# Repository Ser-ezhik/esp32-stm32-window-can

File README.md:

# ESP32 + STM32 window and door controller

New hardware generation of the original `esp32-rp2040-window-rs485` project.
The legacy source and all historic firmware releases remain in Git history and
under the `legacy-rp2040-import` tag. New releases never replace previous binaries.

## Target architecture

- ESP32-S3: CC1101 433 MHz radio, Wi-Fi, web UI, configuration backup and CAN coordinator.
- One cabinet per physical window or door.
- One universal STM32F103C8T6 master in each cabinet: two VNH5019A-E channels, CAN,
  CAP1188 over 4-wire SPI, three D-M9 position sensors and up to three local UART slaves.
- Up to three identical STM32 boards as local slaves, two VNH5019A-E channels per board.
- One firmware image for every STM32 board. `SLOT_ID` pins on the cabinet carrier select
  master/slave role, so a pre-flashed spare module can replace any controller.
- Cabinet identity is stored in a 25LCxx SPI EEPROM on the non-removable carrier board.

## Current development status

The current releases are STM32 two-channel `0.1.0-alpha.14`, STM32 four-channel
`0.1.0-alpha.13`, and ESP32-S3 `0.1.0-alpha.12`:

- hardware bxCAN at 500 kbit/s;
- three hardware UART links at 250 kbit/s with CRC16 frames;
- VNH5019A-E PWM, direction, current sense and diagnostic monitoring;
- CAP1188 4-wire SPI driver, no I2C;
- three active-low D-M9N inputs;
- current disappearance end-stop detection;
- overcurrent, no-current, timeout, edge and communication fail-safe states;
- per-direction full-stroke calibration data and PWM equalization;
- carrier provisioning/discovery protocol;
- watchdog and safe outputs at boot.
- bounded CAN/UART receive work per control-loop pass;
- validation of command, fault and object-type values received from the bus;
- verified internal configuration writes with retries and a latched storage fault;
- ESP32-S3 CAN coordinator with CC1101 receiver and configuration stored in NVS;
- object-based web UI for up to 64 windows/doors, actuator telemetry, events and emergency stop;
- editable 433 MHz button assignments;
- separate open/close calibration, position-aware full-cycle calibration and calibration reset;
- per-input D-M9N/D-M9P polarity stored in the cabinet carrier EEPROM.

The `alpha.1` STM32 binaries and tag remain unchanged. `alpha.2` is a new release
because the CAN protocol gained a calibration-reset command.

ESP32 `alpha.3` fixes mobile-width overflow found during Chrome testing. The
wide actuator table now scrolls inside its own container without widening the page.

ESP32 `alpha.4` targets the tested ESP32-S3 N16R8 module: 16 MB quad Flash,
PSRAM disabled (the firmware does not need it), and a 3 MB application partition. It also prints startup diagnostics
at 115200 baud. This hardware is verified with Arduino-ESP32 core `3.0.7`;
do not use core `3.3.8` for it because Wi-Fi startup is unstable on the tested board.
Generic 4 MB images remain archived under their original tags.

## Build STM32 firmware

Install Arduino CLI and the official STM32 core, then run:

```powershell
arduino-cli compile `
  --fqbn "STMicroelectronics:stm32:GenF1:pnum=GENERIC_F103C8TX,xserial=none,usb=none,opt=oslto,dbg=none,rtlib=nano" `
  --libraries libraries `
  --export-binaries `
  ArduinoIDE\STM32_Universal_Actuator_Node
```

The project deliberately targets the real 64 KiB capacity of STM32F103C8T6 and
does not rely on unofficial 128 KiB clone behaviour.

## Build ESP32-S3 firmware

```powershell
powershell -ExecutionPolicy Bypass -File tools\embed-web.ps1
arduino-cli core install esp32:esp32@3.0.7
arduino-cli compile `
  --fqbn "esp32:esp32:esp32s3:FlashMode=dio,FlashSize=16M,PartitionScheme=app3M_fat9M_16MB,PSRAM=disabled" `
  --libraries libraries `
  --export-binaries ArduinoIDE\ESP32_CC1101_CAN_Master
```

The current web interface intentionally exposes only full open, full close and
stop. A partial ventilation command will be added only after its position rule
or dedicated sensor is defined and bench-tested.

## Documentation

- `docs/HARDWARE_ARCHITECTURE.md`
- `docs/CAN_PROTOCOL.md`
- `docs/SAFETY_AND_RECOVERY.md`
- `docs/BOM_v0.1.md`
- `hardware/DOOR-8CH/README.md`
- `hardware/WINDOW-4CH/README.md`

This is safety-related motion-control software. Test with disconnected mechanics
and current-limited power before connecting a door or window.

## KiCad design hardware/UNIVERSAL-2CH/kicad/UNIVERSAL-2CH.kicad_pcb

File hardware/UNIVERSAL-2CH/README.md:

# UNIVERSAL-2CH

Compact universal carrier for two 12 V linear actuators. The same assembled
board can be provisioned as an optional sliding-door drive or as a two-actuator
vent/window node.

## Hardware

- Board: 106 x 112 mm, four copper layers.
- Controller: one socketed STM32F103C8T6 Mini.
- Drivers: two VNH5019A-E channels with mounting holes for top heatsinks.
- Network: socketed SN65HVD230 CAN transceiver module and protected edge entry.
- Touch safety: optional socketed CAP1188 SPI module with three field inputs.
- Position: three protected reed-switch inputs.
- Identity and journal: 25LC256 carrier EEPROM.
- Supply: socketed MP1584 12 V to 5 V converter, 3.3 V regulator, power-good
  monitor, and logic hold-up capacitor.

## Connectors

- `J1`, `J2`: actuator connectors, `+12V / GND / MA / MB`.
- `J201` to `J203`: open, closed, and in-place reed sensors.
- `J211` to `J213`: capacitive field sensors.
- `J230`: protected 12 V logic input.
- `J240`: `CANH / CANL / GND / shield`.
- `J220`: SWD service header.

All external field connectors are placed on board edges. Power routing and
VNH5019 devices occupy the upper half; CAN and touch electronics are kept away
from the motor outputs.

The field interfaces use board-mounted male headers with removable female cable
plugs. Connector fronts face outwards; the layout includes body clearance
between adjacent plugs and keeps the cable-entry space outside the board edge.

## KiCad Files

- `kicad/UNIVERSAL-2CH.kicad_pcb`: routed PCB.
- `kicad/UNIVERSAL-2CH.kicad_sch`: complete flat schematic.
- `kicad/UNIVERSAL-2CH-multisheet.kicad_sch`: multisheet root schematic.
- `kicad/UNIVERSAL-2CH-routed-top.png`: final top-side 3D render.
- `kicad/UNIVERSAL-2CH-routed-iso.png`: final isometric 3D render.
- `UNIVERSAL-2CH-BOM.csv`: grouped BOM.

## Verification

- PCB DRC: 0 violations, 0 unconnected items.
- Flat schematic ERC: 0 errors, 0 warnings.
- Multisheet schematic ERC: 0 errors, 0 warnings.
- PCB-to-schematic sync: 90 references, 283 connected pads, 38 explicit NCs.
- Routing geometry: straight segments with 45-degree transitions; no staircase
  routing on long connections.
- STM32 pin audit: 27 functional socket connections match `config.h`.
- STM32 build: 24,136 bytes Flash (36%), 3,500 bytes RAM (17%).

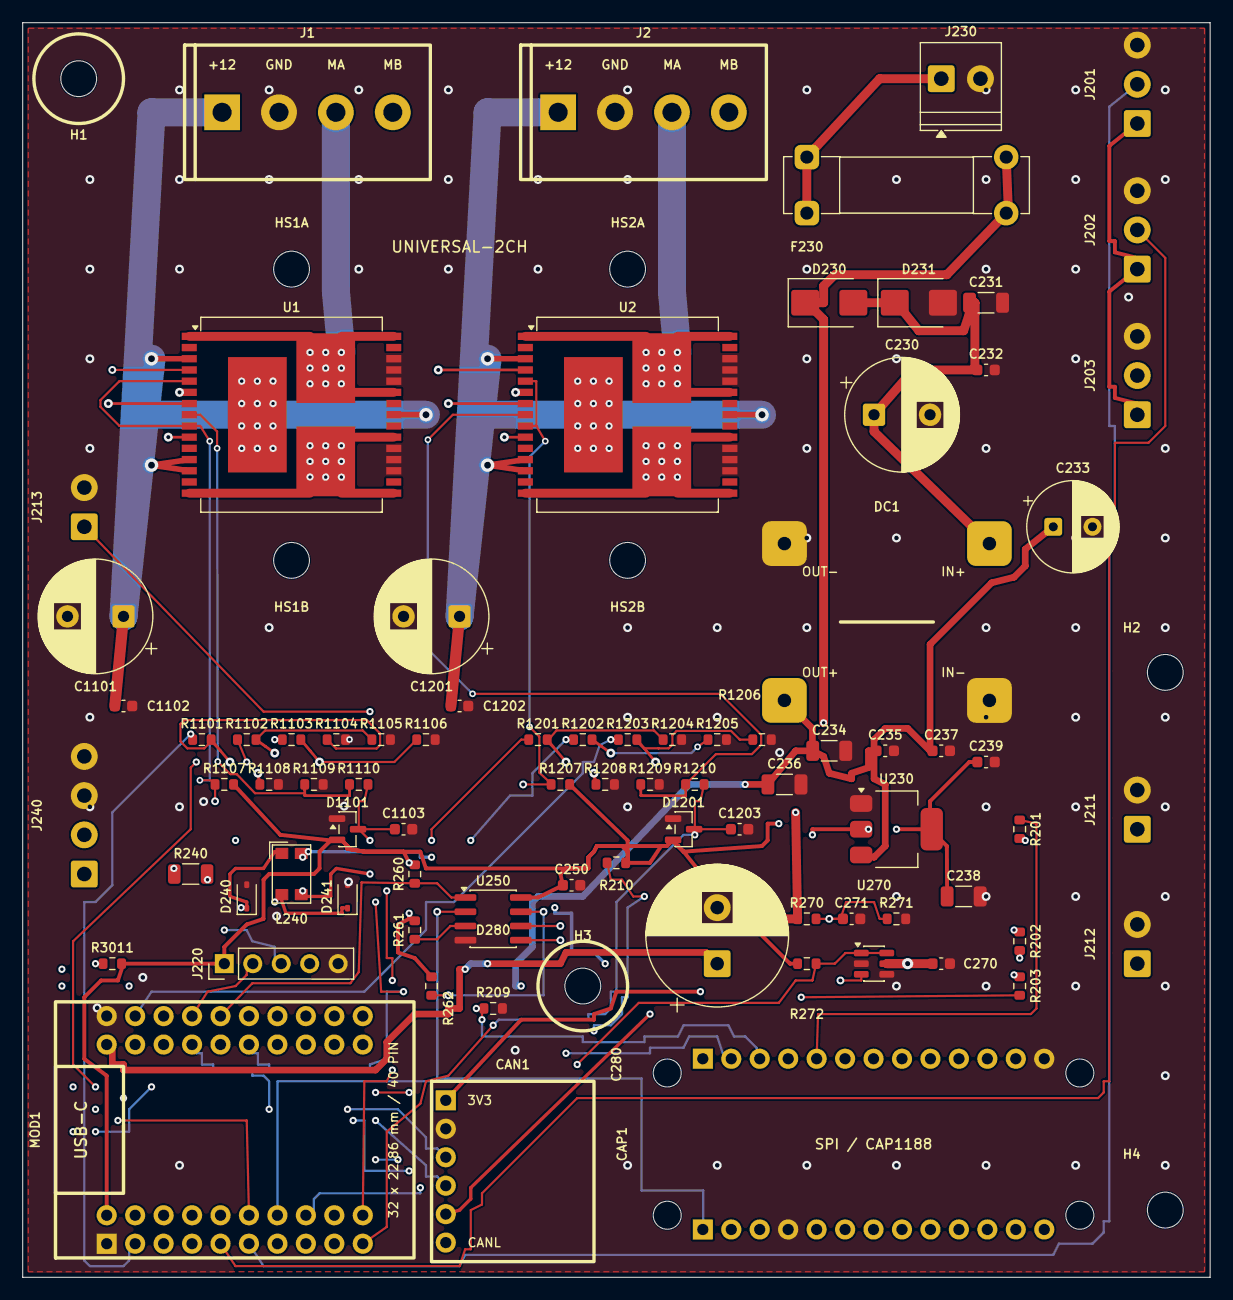
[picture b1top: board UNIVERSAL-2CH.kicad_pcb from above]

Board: 4 copper layers, 106.0 x 112.0 mm, 90 parts (1 on the bottom side), 64 nets.

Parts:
C230: 470UF_50V; CP_Radial_D10.0mm_P5.00mm
C231: 1UF_50V; C_1206_3216Metric
C232: 100NF_50V; C_0603_1608Metric
C233: 220UF_10V; CP_Radial_D8.0mm_P3.50mm
C234: 10UF_10V; C_1206_3216Metric
C235: 100NF_16V; C_0603_1608Metric
C236: 10UF_10V_3V3_IN; C_1206_3216Metric
C237: 100NF_16V_3V3_IN; C_0603_1608Metric
C238: 10UF_10V_3V3_OUT; C_1206_3216Metric
C239: 100NF_16V_3V3_OUT; C_0603_1608Metric
C250: 100NF_EEPROM; C_0603_1608Metric
C270: 100NF_25V_PGOOD_VDD; C_0603_1608Metric
C271: 100NF_PGOOD_FILTER; C_0603_1608Metric
C280: 4700UF_10V_LOW_ESR_S1_HOLDUP; CP_Radial_D12.5mm_P5.00mm
C1101, C1201: 470uF 35V LOW_ESR; CP_Radial_D10.0mm_P5.00mm
C1102, C1202: 100nF 50V X7R VCC; C_0603_1608Metric
C1103, C1203: 100nF ADC_FILTER; C_0603_1608Metric
CAN1: SN65HVD230_MASTER_CAN; SN65HVD230_Module_14.5x16.1mm_1x06
CAP1: CAP1188_SPI; CAP1188_Adafruit1602_Module_2x13
D230: SS54_REVERSE_POLARITY; D_SMB
D231: SMBJ16A_TVS; D_SMB
D240: PESD1CAN_CANH; D_SOD-323
D241: PESD1CAN_CANL; D_SOD-323
D280: SS34_S1_HOLDUP_ISOLATION; D_SMA
D1101, D1201: BAT54S ADC_CLAMP; SOT-23
DC1: MP1584_FIXED_5V; MP1584_Fixed5V_Module_22.3x17mm
F230: 1A_SLOW_5X20; Fuseholder_Clip-5x20mm_Bel_FC-203-22_Lateral_P17.80x5.00mm_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
H1, H2, H3, H4: M3.2_NPTH; MountingHole_M3_2_NPTH
HS1A, HS1B, HS2A, HS2B: M3.2 NPTH, TOP HEATSINK; MountingHole_3.2mm_M3
J1: ACTUATOR_CH1_4P; DINKLE_2EHDRC-04P_P5.08mm
J2: ACTUATOR_CH2_4P; DINKLE_2EHDRC-04P_P5.08mm
J201: REED_A_OPEN_3V3_SIG_GND; TerminalBlock_Phoenix_PT-1,5-3-3.5-H_1x03_P3.50mm_Horizontal
J202: REED_A_CLOSED_3V3_SIG_GND; TerminalBlock_Phoenix_PT-1,5-3-3.5-H_1x03_P3.50mm_Horizontal
J203: REED_A_IN_PLACE_3V3_SIG_GND; TerminalBlock_Phoenix_PT-1,5-3-3.5-H_1x03_P3.50mm_Horizontal
J211: CAP_CS1_GND; TerminalBlock_Phoenix_PT-1,5-2-3.5-H_1x02_P3.50mm_Horizontal
J212: CAP_CS2_GND; TerminalBlock_Phoenix_PT-1,5-2-3.5-H_1x02_P3.50mm_Horizontal
J213: CAP_CS3_GND; TerminalBlock_Phoenix_PT-1,5-2-3.5-H_1x02_P3.50mm_Horizontal
J220: SWD_S1_3V3_DIO_CLK_NRST_GND; PinHeader_1x05_P2.54mm_Vertical
J230: LOGIC_12V_GND; TerminalBlock_Phoenix_PT-1,5-2-3.5-H_1x02_P3.50mm_Horizontal
J240: CANH_CANL_GND_SHIELD; TerminalBlock_Phoenix_PT-1,5-4-3.5-H_1x04_P3.50mm_Horizontal
L240: CMC_CAN; L_CommonModeChoke_Coilcraft_1812CAN
MOD1: STM32F103C8T6_MINI_SLOT_S1; STM32F103C8T6_Mini_CH340_4x10
R201, R202, R203: 1K_CAP_INPUT; R_0603_1608Metric
R209: 10K_CAP_RESET_PULLDOWN; R_0603_1608Metric
R210: 10K_CAP_IRQ_PULLUP; R_0603_1608Metric
R240: 120R_CAN_TERM_DNP; R_1206_3216Metric
R260: 10K_EEPROM_CS_PULLUP; R_0603_1608Metric
R261: 10K_EEPROM_WP_PULLUP; R_0603_1608Metric
R262: 10K_EEPROM_HOLD_PULLUP; R_0603_1608Metric
R270: 226K_1%_PGOOD_TOP; R_0603_1608Metric
R271: 10K_1%_PGOOD_BOTTOM; R_0603_1608Metric
R272: 10K_PGOOD_PULLUP; R_0603_1608Metric
R1101, R1201: 100R INA_SER; R_0603_1608Metric
R1102, R1202: 100R INB_SER; R_0603_1608Metric
R1103, R1203: 100R PWM_SER; R_0603_1608Metric
R1104, R1204: 10K INA_PULLDOWN; R_0603_1608Metric
R1105, R1205: 10K INB_PULLDOWN; R_0603_1608Metric
R1106, R1206: 10K PWM_PULLDOWN; R_0603_1608Metric
R1107, R1207: 4K7 DIAG_PULLUP; R_0603_1608Metric
R1108, R1208: 10K CS_DIS_PULLDOWN; R_0603_1608Metric
R1109, R1209: 1K 1% CS_LOAD; R_0603_1608Metric
R1110, R1210: 10K ADC_SERIES; R_0603_1608Metric
R3011: 47K SLOT_S1_ID0; R_0603_1608Metric
U1, U2: VNH5019A-E; ST_MultiPowerSO-30
U230: AMS1117-3V3; SOT-223-3_TabPin2
U250: 25LC256_SOIC8_CARRIER_ID; SOIC-8_3.9x4.9mm_P1.27mm
U270: TLV6700DDCR_POWER_MONITOR; SOT-23-6

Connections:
CANH_BUS: CAN1.5, L240.4, R240.1
CANH_ENTRY: D240.1, J240.1, L240.1
CANL_BUS: CAN1.6, L240.3, R240.2
CANL_ENTRY: D241.1, J240.2, L240.2
CAP_C1_FIELD: J211.1, R201.2
CAP_C1_RAW: CAP1.18, R201.1
CAP_C2_FIELD: J212.1, R202.2
CAP_C2_RAW: CAP1.19, R202.1
CAP_C3_FIELD: J213.1, R203.2
CAP_C3_RAW: CAP1.20, R203.1
CAP_CS: CAP1.15, MOD1.18
CAP_IRQ: MOD1.13, R210.1
CAP_MISO: CAP1.1, MOD1.17, U250.2
CAP_MOSI: CAP1.14, MOD1.7, U250.5
CAP_RESET: CAP1.16, MOD1.29, R209.1
CAP_SCK: CAP1.2, MOD1.8, U250.6
CH1_CS_DIS: R1108.1, U1.6
CH1_CS_RAW: R1109.1, R1110.1, U1.8
CH1_CURRENT_ADC: C1103.1, D1101.3, MOD1.20, R1110.2
CH1_DIAG: MOD1.27, R1107.1, U1.5, U1.9
CH1_INA: R1101.2, R1104.1, U1.4
CH1_INA_MCU: MOD1.2, R1101.1
CH1_INB: R1102.2, R1105.1, U1.10
CH1_INB_MCU: MOD1.12, R1102.1
CH1_OUTA: J1.3, U1.1, U1.25, U1.30, U1.33
CH1_OUTB: J1.4, U1.15, U1.16, U1.21, U1.32
CH1_PWM: R1103.2, R1106.1, U1.7
CH1_PWM_MCU: MOD1.22, R1103.1
CH2_CS_DIS: R1208.1, U2.6
CH2_CS_RAW: R1209.1, R1210.1, U2.8
CH2_CURRENT_ADC: C1203.1, D1201.3, MOD1.10, R1210.2
CH2_DIAG: MOD1.3, R1207.1, U2.5, U2.9
CH2_INA: R1201.2, R1204.1, U2.4
CH2_INA_MCU: MOD1.26, R1201.1
CH2_INB: R1202.2, R1205.1, U2.10
CH2_INB_MCU: MOD1.36, R1202.1
CH2_OUTA: J2.3, U2.1, U2.25, U2.30, U2.33
CH2_OUTB: J2.4, U2.15, U2.16, U2.21, U2.32
CH2_PWM: R1203.2, R1206.1, U2.7
CH2_PWM_MCU: MOD1.32, R1203.1
EEPROM_CS: MOD1.35, R260.1, U250.1
EEPROM_HOLD: R262.1, U250.7
EEPROM_WP: R261.1, U250.3
FUSED_12V_CH1: C1101.1, C1102.1, J1.1, U1.3, U1.12, U1.13, U1.23, U1.31
FUSED_12V_CH2: C1201.1, C1202.1, J2.1, U2.3, U2.12, U2.13, U2.23, U2.31
GND: C230.2, C231.2, C232.2, C233.2, C234.2, C235.2, C236.2, C237.2, C238.2, C239.2, C250.2, C270.2, C271.2, C280.2, C1101.2, C1102.2, C1103.2, C1201.2, C1202.2, C1203.2, CAN1.2, CAP1.4, CAP1.26, D231.2, D240.2, D241.2, D1101.1, D1201.1, DC1.2, DC1.4, J1.2, J2.2, J201.3, J202.3, J203.3, J211.2, J212.2, J213.2, J220.5, J230.2, J240.3, J240.4, MOD1.1, MOD1.31, R209.2, R271.2, R1104.2, R1105.2, R1106.2, R1108.2, R1109.2, R1204.2, R1205.2, R1206.2, R1208.2, R1209.2, U1.18, U1.19, U1.20, U1.26, U1.27, U1.28, U2.18, U2.19, U2.20, U2.26, U2.27, U2.28, U230.1, U250.4, U270.2, U270.4
LOGIC_3V3: C238.1, C239.1, CAN1.1, U230.2
LOGIC_5V: C233.1, C234.1, C235.1, C236.1, C237.1, CAP1.3, D280.2, DC1.3, U230.3
LOGIC_12V_FUSED: C270.1, D230.1, F230.2, R270.1, U270.5
LOGIC_12V_IN: F230.1, J230.1
LOGIC_12V_PROTECTED: C230.1, C231.1, C232.1, D230.2, D231.1, DC1.1
PGOOD_SENSE: C271.1, R270.2, R271.1, U270.3
POWER_GOOD: MOD1.30, R272.2, U270.1, U270.6
REED_A_CLOSED: J202.2, MOD1.5
REED_A_IN_PLACE: J203.2, MOD1.38
REED_A_OPEN: J201.2, MOD1.6
S1_3V3: C250.1, D1101.2, D1201.2, J201.1, J202.1, J203.1, J220.1, MOD1.11, R210.2, R260.2, R261.2, R262.2, R272.1, R1107.2, R1207.2, R3011.2, U250.8
S1_5V_HOLD: C280.1, D280.1, MOD1.21
S1_CAN_RX: CAN1.4, MOD1.33
S1_CAN_TX: CAN1.3, MOD1.24
S1_NRST: J220.4, MOD1.16
S1_SLOT_ID0: MOD1.15, R3011.1
S1_SWCLK: J220.3, MOD1.25
S1_SWDIO: J220.2, MOD1.34

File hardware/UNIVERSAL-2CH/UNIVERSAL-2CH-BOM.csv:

"Value","References","Footprint","Quantity"
"100NF_16V","C235","C_0603_1608Metric","1"
"100NF_16V_3V3_IN","C237","C_0603_1608Metric","1"
"100NF_16V_3V3_OUT","C239","C_0603_1608Metric","1"
"100NF_25V_PGOOD_VDD","C270","C_0603_1608Metric","1"
"100NF_50V","C232","C_0603_1608Metric","1"
"100NF_EEPROM","C250","C_0603_1608Metric","1"
"100NF_PGOOD_FILTER","C271","C_0603_1608Metric","1"
"100R INA_SER","R1101,R1201","R_0603_1608Metric","2"
"100R INB_SER","R1102,R1202","R_0603_1608Metric","2"
"100R PWM_SER","R1103,R1203","R_0603_1608Metric","2"
"100nF 50V X7R VCC","C1102,C1202","C_0603_1608Metric","2"
"100nF ADC_FILTER","C1103,C1203","C_0603_1608Metric","2"
"10K ADC_SERIES","R1110,R1210","R_0603_1608Metric","2"
"10K CS_DIS_PULLDOWN","R1108,R1208","R_0603_1608Metric","2"
"10K INA_PULLDOWN","R1104,R1204","R_0603_1608Metric","2"
"10K INB_PULLDOWN","R1105,R1205","R_0603_1608Metric","2"
"10K PWM_PULLDOWN","R1106,R1206","R_0603_1608Metric","2"
"10K_1%_PGOOD_BOTTOM","R271","R_0603_1608Metric","1"
"10K_CAP_IRQ_PULLUP","R210","R_0603_1608Metric","1"
"10K_CAP_RESET_PULLDOWN","R209","R_0603_1608Metric","1"
"10K_EEPROM_CS_PULLUP","R260","R_0603_1608Metric","1"
"10K_EEPROM_HOLD_PULLUP","R262","R_0603_1608Metric","1"
"10K_EEPROM_WP_PULLUP","R261","R_0603_1608Metric","1"
"10K_PGOOD_PULLUP","R272","R_0603_1608Metric","1"
"10UF_10V","C234","C_1206_3216Metric","1"
"10UF_10V_3V3_IN","C236","C_1206_3216Metric","1"
"10UF_10V_3V3_OUT","C238","C_1206_3216Metric","1"
"120R_CAN_TERM_DNP","R240","R_1206_3216Metric","1"
"1A_SLOW_5X20","F230","Fuseholder_Clip-5x20mm_Bel_FC-203-22_Lateral_P17.80x5.00mm_D1.17mm_Horizontal","1"
"1K 1% CS_LOAD","R1109,R1209","R_0603_1608Metric","2"
"1K_CAP_INPUT","R201,R202,R203","R_0603_1608Metric","3"
"1UF_50V","C231","C_1206_3216Metric","1"
"220UF_10V","C233","CP_Radial_D8.0mm_P3.50mm","1"
"226K_1%_PGOOD_TOP","R270","R_0603_1608Metric","1"
"25LC256_SOIC8_CARRIER_ID","U250","SOIC-8_3.9x4.9mm_P1.27mm","1"
"4700UF_10V_LOW_ESR_S1_HOLDUP","C280","CP_Radial_D12.5mm_P5.00mm","1"
"470UF_50V","C230","CP_Radial_D10.0mm_P5.00mm","1"
"470uF 35V LOW_ESR","C1101,C1201","CP_Radial_D10.0mm_P5.00mm","2"
"47K SLOT_S1_ID0","R3011","R_0603_1608Metric","1"
"4K7 DIAG_PULLUP","R1107,R1207","R_0603_1608Metric","2"
"ACTUATOR_CH1_4P","J1","DINKLE_2EHDRC-04P_P5.08mm","1"
"ACTUATOR_CH2_4P","J2","DINKLE_2EHDRC-04P_P5.08mm","1"
"AMS1117-3V3","U230","SOT-223-3_TabPin2","1"
"BAT54S ADC_CLAMP","D1101,D1201","SOT-23","2"
"CANH_CANL_GND_SHIELD","J240","TerminalBlock_Phoenix_PT-1,5-4-3.5-H_1x04_P3.50mm_Horizontal","1"
"CAP1188_SPI","CAP1","CAP1188_Adafruit1602_Module_2x13","1"
"CAP_CS1_GND","J211","TerminalBlock_Phoenix_PT-1,5-2-3.5-H_1x02_P3.50mm_Horizontal","1"
"CAP_CS2_GND","J212","TerminalBlock_Phoenix_PT-1,5-2-3.5-H_1x02_P3.50mm_Horizontal","1"
"CAP_CS3_GND","J213","TerminalBlock_Phoenix_PT-1,5-2-3.5-H_1x02_P3.50mm_Horizontal","1"
"CMC_CAN","L240","L_CommonModeChoke_Coilcraft_1812CAN","1"
"LOGIC_12V_GND","J230","TerminalBlock_Phoenix_PT-1,5-2-3.5-H_1x02_P3.50mm_Horizontal","1"
"M3.2 NPTH, TOP HEATSINK","HS1A,HS1B,HS2A,HS2B","MountingHole_3.2mm_M3","4"
"M3.2_NPTH","H1,H2,H3,H4","MountingHole_M3_2_NPTH","4"
"MP1584_FIXED_5V","DC1","MP1584_Fixed5V_Module_22.3x17mm","1"
"PESD1CAN_CANH","D240","D_SOD-323","1"
"PESD1CAN_CANL","D241","D_SOD-323","1"
"REED_A_CLOSED_3V3_SIG_GND","J202","TerminalBlock_Phoenix_PT-1,5-3-3.5-H_1x03_P3.50mm_Horizontal","1"
"REED_A_IN_PLACE_3V3_SIG_GND","J203","TerminalBlock_Phoenix_PT-1,5-3-3.5-H_1x03_P3.50mm_Horizontal","1"
"REED_A_OPEN_3V3_SIG_GND","J201","TerminalBlock_Phoenix_PT-1,5-3-3.5-H_1x03_P3.50mm_Horizontal","1"
"SMBJ16A_TVS","D231","D_SMB","1"
"SN65HVD230_MASTER_CAN","CAN1","SN65HVD230_Module_14.5x16.1mm_1x06","1"
"SS34_S1_HOLDUP_ISOLATION","D280","D_SMA","1"
"SS54_REVERSE_POLARITY","D230","D_SMB","1"
"STM32F103C8T6_MINI_SLOT_S1","MOD1","STM32F103C8T6_Mini_CH340_4x10","1"
"SWD_S1_3V3_DIO_CLK_NRST_GND","J220","PinHeader_1x05_P2.54mm_Vertical","1"
"TLV6700DDCR_POWER_MONITOR","U270","SOT-23-6","1"
"VNH5019A-E","U1,U2","ST_MultiPowerSO-30","2"

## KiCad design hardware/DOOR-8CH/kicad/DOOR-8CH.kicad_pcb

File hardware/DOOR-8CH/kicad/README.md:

# KiCad source: DOOR-8CH

`DOOR-8CH.kicad_pcb` is the editable KiCad 10 board source, started from the
approved universal one-board-per-cabinet architecture. It presently contains:

- the provisional 260 x 160 mm outline;
- the four board mounting holes, M3.2 NPTH;
- a four-layer stack-up declaration;
- mechanically checked placement for S1 through S4 and the photographed
  plug-in modules.

The editable source is also the basis of the checked v1.43 fabrication release. The v1.43
board contains the repeated VNH passive blocks, slot straps, named power,
motor, control, diagnostic, current-sense and low-voltage communication nets.
The routed PCB passes DRC with zero violations and zero unconnected pads.

Two electrically equivalent principle-schematic views are included:

- `DOOR-8CH.kicad_sch` is the complete flat schematic;
- `DOOR-8CH-multisheet.kicad_sch` is the recommended entry point, split into
  power, control/CAN, CAP1188, reeds, eight actuator channels and mechanical
  sheets.

Both schematic views are generated from the routed PCB and verified by
`tools/verify_door8ch_schematic_sync.py`. The firmware comparison is recorded
in `../SCHEMATIC_FIRMWARE_AUDIT.md`.

The placement already uses KiCad's verified `ST_MultiPowerSO-30` footprint for
all eight VNH5019A-E devices, `Phoenix MKDS-3-2-5.08` two-way power terminals,
and one-piece 4x10 / 2.54 mm socket footprints for each STM32 module. Each VNH
has one dedicated fused 12 V terminal and one actuator-output terminal. The 26 mm
heatsink-hole pair is above and below its VNH, avoiding overlap with a
neighbouring channel.

Each VNH now has three 100 Ohm input resistors, reset-safe pull-downs, a 4.7
kOhm diagnostic pull-up, CS_DIS pull-down, 1 kOhm current-sense load, protected
and filtered ADC input, 470 uF local bulk capacitor and 100 nF ceramic bypass.
The PB2/PA7 slot straps are also present and match the universal firmware.
The low-voltage stage also includes the MP1584 input/output nets, a carrier
3.3 V regulator, CAN trunk connector with choke/ESD/optional termination,
both SN65HVD230 modules, 25LC256 carrier EEPROM, CAP1188 SPI and field-sensor nets, six reed
connectors, ESP32-S3 power/CAN, CC1101 SPI/GDO lines and the internal UART
links between S1 and S2-S4. In v0.7 the CAN trunk entry and its protection
parts are moved to the lower service area beside `CAN2`, and `MOD3` is shifted
right to keep that CAN area away from the actuator power terminals.

Version v1.41 adds U270 (`TLV6700DDCR`) on the fused 12 V logic input, an
open-drain `POWER_GOOD` connection to S1 PC13, and an isolated MASTER hold-up
rail using D280 (`SS34`) and C280 (4700 uF / 10 V low ESR). U250 and its SPI
pull-ups are powered by the held `S1_3V3` rail so an outage record can finish.

Version v1.43 corrects D230 so its anode is connected to
`LOGIC_12V_FUSED` and its cathode to `LOGIC_12V_PROTECTED`. It also adds the
front-silkscreen Telegram QR code and exports an SMD-only JLCPCB assembly set
with package-specific orientation corrections.

Version v1.44 combines each channel's fused 12 V input and bidirectional motor
output into one keyed DINKLE 2EHDRC-04P connector. Pins are `+12V`, `GND`, `MA`
and `MB`; all resistor and capacitor references are visible on front silk.

Version v1.47 corrects the YD ESP32-S3 N16R8 socket to 25.40 mm row spacing,
keeps 1.00 mm finished drills, and reroutes the nearby CAN and reed signals.
The resulting PCB passes DRC with zero violations and zero unconnected items.

All eight actuator terminals are on the top edge. STM32 USB-C connectors face the
bottom service edge, both ESP32-S3 USB connectors face the left edge, the
CC1101 antenna faces the left edge, and CAP1188 touch-channel pins face the
right edge. The placement uses complete photo-matched footprints for the two
SN65HVD230 modules, CC1101 and CAP1188, plus the photographed 44-pin YD
ESP32-S3 N16R8 board with 25.40 mm row spacing. KiCad placement DRC reports
zero violations.

## Before fabrication

1. Verify all photographed module footprints, row orientation and connector
   polarity on 1:1 prints and physical samples.
2. Populate one VNH5019 channel and calibrate the current-sense conversion and
   protection thresholds before releasing production Gerbers.
3. Measure the C280 hold-up time at cold temperature and maximum MASTER load;
   verify a complete U250 write after removing 12 V repeatedly.

The older `ACT-CARRIER-2CH` files remain an archived design study and must not
be used for fabrication.

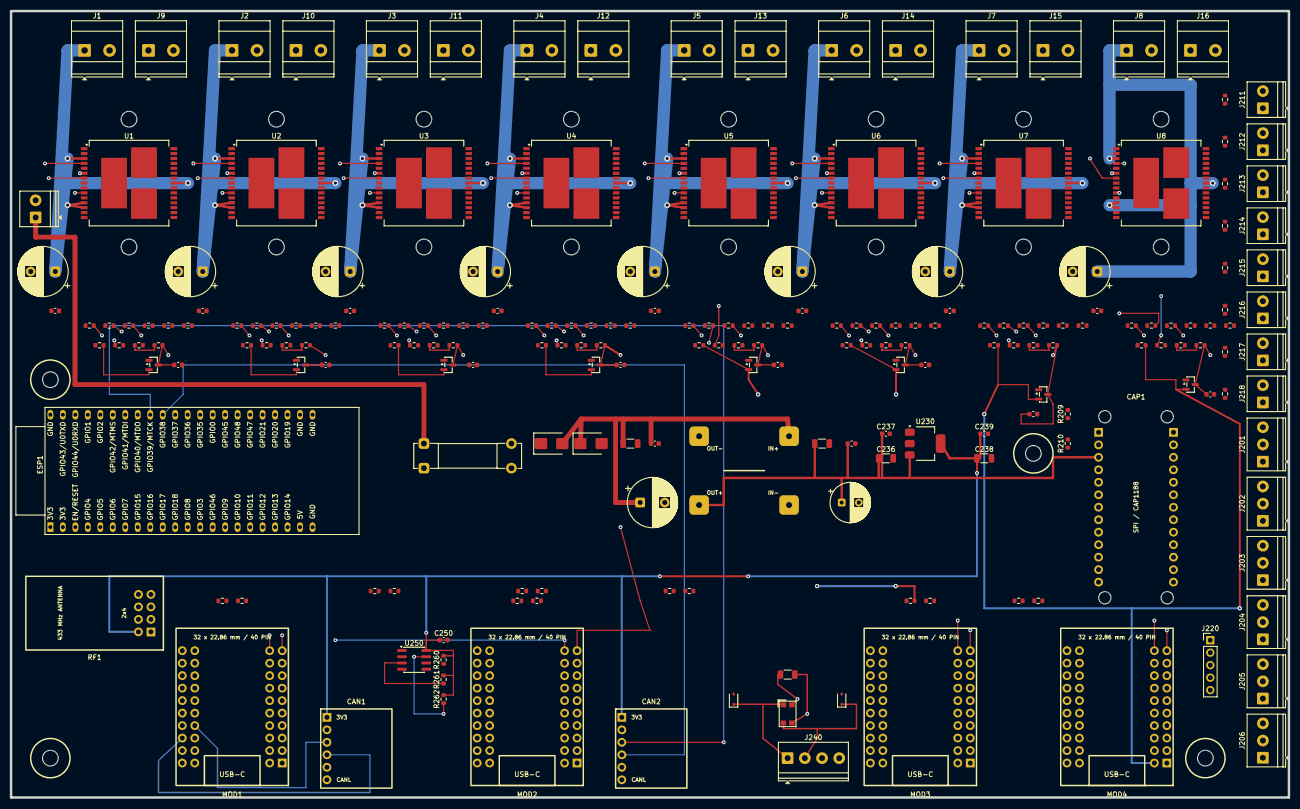
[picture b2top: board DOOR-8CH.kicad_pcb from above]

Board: 4 copper layers, 260.0 x 160.0 mm, 230 parts (0 on the bottom side), 181 nets.

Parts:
C230: 470UF_50V; CP_Radial_D10.0mm_P5.00mm
C231: 1UF_50V; C_1206_3216Metric
C232: 100NF_50V; C_0603_1608Metric
C233: 220UF_10V; CP_Radial_D8.0mm_P3.50mm
C234: 10UF_10V; C_1206_3216Metric
C235: 100NF_16V; C_0603_1608Metric
C236: 10UF_10V_3V3_IN; C_1206_3216Metric
C237: 100NF_16V_3V3_IN; C_0603_1608Metric
C238: 10UF_10V_3V3_OUT; C_1206_3216Metric
C239: 100NF_16V_3V3_OUT; C_0603_1608Metric
C250: 100NF_EEPROM; C_0603_1608Metric
C1101, C1201, C1301, C1401, C1501, C1601, C1701, C1801: 470uF 35V LOW_ESR; CP_Radial_D10.0mm_P5.00mm
C1102, C1202, C1302, C1402, C1502, C1602, C1702, C1802: 100nF 50V X7R VCC; C_0603_1608Metric
C1103, C1203, C1303, C1403, C1503, C1603, C1703, C1803: 100nF ADC_FILTER; C_0603_1608Metric
CAN1: SN65HVD230_MASTER_CAN; SN65HVD230_Module_14.5x16.1mm_1x06
CAN2: SN65HVD230_ESP_CAN_OPTION; SN65HVD230_Module_14.5x16.1mm_1x06
CAP1: CAP1188_SPI; CAP1188_Adafruit1602_Module_2x13
D230: SS54_REVERSE_POLARITY; D_SMB
D231: SMBJ16A_TVS; D_SMB
D240: PESD1CAN_CANH; D_SOD-323
D241: PESD1CAN_CANL; D_SOD-323
D1101, D1201, D1301, D1401, D1501, D1601, D1701, D1801: BAT54S ADC_CLAMP; SOT-23
DC1: MP1584_FIXED_5V; MP1584_Fixed5V_Module_22.3x17mm
ESP1: ESP32_S3_DEVKITC_DOUBLE_DOOR_ONLY; ESP32-S3-DevKitC
F230: 1A_SLOW_5X20; Fuseholder_Clip-5x20mm_Bel_FC-203-22_Lateral_P17.80x5.00mm_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
H1, H2, H3, H4: M3.2_NPTH; MountingHole_M3_2_NPTH
HS1A, HS1B, HS2A, HS2B, HS3A, HS3B, HS4A, HS4B, HS5A, HS5B, HS6A, HS6B, HS7A, HS7B, HS8A, HS8B: M3.2 NPTH, TOP HEATSINK; MountingHole_3.2mm_M3
J1: FUSED_12V_CH1; TerminalBlock_Phoenix_MKDS-3-2-5.08_1x02_P5.08mm_Horizontal
J2: FUSED_12V_CH2; TerminalBlock_Phoenix_MKDS-3-2-5.08_1x02_P5.08mm_Horizontal
J3: FUSED_12V_CH3; TerminalBlock_Phoenix_MKDS-3-2-5.08_1x02_P5.08mm_Horizontal
J4: FUSED_12V_CH4; TerminalBlock_Phoenix_MKDS-3-2-5.08_1x02_P5.08mm_Horizontal
J5: FUSED_12V_CH5; TerminalBlock_Phoenix_MKDS-3-2-5.08_1x02_P5.08mm_Horizontal
J6: FUSED_12V_CH6; TerminalBlock_Phoenix_MKDS-3-2-5.08_1x02_P5.08mm_Horizontal
J7: FUSED_12V_CH7; TerminalBlock_Phoenix_MKDS-3-2-5.08_1x02_P5.08mm_Horizontal
J8: FUSED_12V_CH8; TerminalBlock_Phoenix_MKDS-3-2-5.08_1x02_P5.08mm_Horizontal
J9: ACTUATOR_CH1; TerminalBlock_Phoenix_MKDS-3-2-5.08_1x02_P5.08mm_Horizontal
J10: ACTUATOR_CH2; TerminalBlock_Phoenix_MKDS-3-2-5.08_1x02_P5.08mm_Horizontal
J11: ACTUATOR_CH3; TerminalBlock_Phoenix_MKDS-3-2-5.08_1x02_P5.08mm_Horizontal
J12: ACTUATOR_CH4; TerminalBlock_Phoenix_MKDS-3-2-5.08_1x02_P5.08mm_Horizontal
J13: ACTUATOR_CH5; TerminalBlock_Phoenix_MKDS-3-2-5.08_1x02_P5.08mm_Horizontal
J14: ACTUATOR_CH6; TerminalBlock_Phoenix_MKDS-3-2-5.08_1x02_P5.08mm_Horizontal
J15: ACTUATOR_CH7; TerminalBlock_Phoenix_MKDS-3-2-5.08_1x02_P5.08mm_Horizontal
J16: ACTUATOR_CH8; TerminalBlock_Phoenix_MKDS-3-2-5.08_1x02_P5.08mm_Horizontal
J201: REED_A_OPEN_3V3_SIG_GND; TerminalBlock_Phoenix_PT-1,5-3-3.5-H_1x03_P3.50mm_Horizontal
J202: REED_A_CLOSED_3V3_SIG_GND; TerminalBlock_Phoenix_PT-1,5-3-3.5-H_1x03_P3.50mm_Horizontal
J203: REED_A_IN_PLACE_3V3_SIG_GND; TerminalBlock_Phoenix_PT-1,5-3-3.5-H_1x03_P3.50mm_Horizontal
J204: REED_B_OPEN_3V3_SIG_GND; TerminalBlock_Phoenix_PT-1,5-3-3.5-H_1x03_P3.50mm_Horizontal
J205: REED_B_CLOSED_3V3_SIG_GND; TerminalBlock_Phoenix_PT-1,5-3-3.5-H_1x03_P3.50mm_Horizontal
J206: REED_B_IN_PLACE_3V3_SIG_GND; TerminalBlock_Phoenix_PT-1,5-3-3.5-H_1x03_P3.50mm_Horizontal
J211: CAP_CS1_GND; TerminalBlock_Phoenix_PT-1,5-2-3.5-H_1x02_P3.50mm_Horizontal
J212: CAP_CS2_GND; TerminalBlock_Phoenix_PT-1,5-2-3.5-H_1x02_P3.50mm_Horizontal
J213: CAP_CS3_GND; TerminalBlock_Phoenix_PT-1,5-2-3.5-H_1x02_P3.50mm_Horizontal
J214: CAP_CS4_GND; TerminalBlock_Phoenix_PT-1,5-2-3.5-H_1x02_P3.50mm_Horizontal
J215: CAP_CS5_GND; TerminalBlock_Phoenix_PT-1,5-2-3.5-H_1x02_P3.50mm_Horizontal
J216: CAP_CS6_GND; TerminalBlock_Phoenix_PT-1,5-2-3.5-H_1x02_P3.50mm_Horizontal
J217: CAP_CS7_GND; TerminalBlock_Phoenix_PT-1,5-2-3.5-H_1x02_P3.50mm_Horizontal
J218: CAP_CS8_GND; TerminalBlock_Phoenix_PT-1,5-2-3.5-H_1x02_P3.50mm_Horizontal
J220: SWD_S1_3V3_DIO_CLK_NRST_GND; PinHeader_1x05_P2.54mm_Vertical
J230: LOGIC_12V_GND; TerminalBlock_Phoenix_PT-1,5-2-3.5-H_1x02_P3.50mm_Horizontal
J240: CANH_CANL_GND_SHIELD; TerminalBlock_Phoenix_PT-1,5-4-3.5-H_1x04_P3.50mm_Horizontal
L240: CMC_CAN; L_CommonModeChoke_Coilcraft_1812CAN
MOD1: STM32F103C8T6_MINI_SLOT_S1; STM32F103C8T6_Mini_CH340_4x10
MOD2: STM32F103C8T6_MINI_SLOT_S2; STM32F103C8T6_Mini_CH340_4x10
MOD3: STM32F103C8T6_MINI_SLOT_S3; STM32F103C8T6_Mini_CH340_4x10
MOD4: STM32F103C8T6_MINI_SLOT_S4; STM32F103C8T6_Mini_CH340_4x10
R201, R202, R203, R204, R205, R206, R207, R208: 1K_CAP_INPUT; R_0603_1608Metric
R209: 10K_CAP_RESET_PULLDOWN; R_0603_1608Metric
R210: 10K_CAP_IRQ_PULLUP; R_0603_1608Metric
R240: 120R_CAN_TERM_DNP; R_1206_3216Metric
R250, R251, R252, R253, R254, R255: 100R_UART_TX; R_0603_1608Metric
R260: 10K_EEPROM_CS_PULLUP; R_0603_1608Metric
R261: 10K_EEPROM_WP_PULLUP; R_0603_1608Metric
R262: 10K_EEPROM_HOLD_PULLUP; R_0603_1608Metric
R1101, R1201, R1301, R1401, R1501, R1601, R1701, R1801: 100R INA_SER; R_0603_1608Metric
R1102, R1202, R1302, R1402, R1502, R1602, R1702, R1802: 100R INB_SER; R_0603_1608Metric
R1103, R1203, R1303, R1403, R1503, R1603, R1703, R1803: 100R PWM_SER; R_0603_1608Metric
R1104, R1204, R1304, R1404, R1504, R1604, R1704, R1804: 10K INA_PULLDOWN; R_0603_1608Metric
R1105, R1205, R1305, R1405, R1505, R1605, R1705, R1805: 10K INB_PULLDOWN; R_0603_1608Metric
R1106, R1206, R1306, R1406, R1506, R1606, R1706, R1806: 10K PWM_PULLDOWN; R_0603_1608Metric
R1107, R1207, R1307, R1407, R1507, R1607, R1707, R1807: 4K7 DIAG_PULLUP; R_0603_1608Metric
R1108, R1208, R1308, R1408, R1508, R1608, R1708, R1808: 10K CS_DIS_PULLDOWN; R_0603_1608Metric
R1109, R1209, R1309, R1409, R1509, R1609, R1709, R1809: 1K 1% CS_LOAD; R_0603_1608Metric
R1110, R1210, R1310, R1410, R1510, R1610, R1710, R1810: 10K ADC_SERIES; R_0603_1608Metric
R3011: 47K SLOT_S1_ID0; R_0603_1608Metric
R3012: 47K SLOT_S1_ID1; R_0603_1608Metric
R3021: 0R SLOT_S2_ID0; R_0603_1608Metric
R3022: 47K SLOT_S2_ID1; R_0603_1608Metric
R3031: 47K SLOT_S3_ID0; R_0603_1608Metric
R3032: 0R SLOT_S3_ID1; R_0603_1608Metric
R3041: 0R SLOT_S4_ID0; R_0603_1608Metric
R3042: 0R SLOT_S4_ID1; R_0603_1608Metric
RF1: CC1101_433MHZ; CC1101_433MHz_Module_28x15mm_2x04
U1, U2, U3, U4, U5, U6, U7, U8: VNH5019A-E; ST_MultiPowerSO-30
U230: AMS1117-3V3; SOT-223-3_TabPin2
U250: 25LC256_SOIC8_CARRIER_ID; SOIC-8_3.9x4.9mm_P1.27mm

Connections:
CANH_BUS: CAN1.5, CAN2.5, L240.4, R240.1
CANH_ENTRY: D240.1, J240.1, L240.1
CANL_BUS: CAN1.6, CAN2.6, L240.3, R240.2
CANL_ENTRY: D241.1, J240.2, L240.2
CAP_C1_FIELD: J211.1, R201.2
CAP_C1_RAW: CAP1.18, R201.1
CAP_C2_FIELD: J212.1, R202.2
CAP_C2_RAW: CAP1.19, R202.1
CAP_C3_FIELD: J213.1, R203.2
CAP_C3_RAW: CAP1.20, R203.1
CAP_C4_FIELD: J214.1, R204.2
CAP_C4_RAW: CAP1.21, R204.1
CAP_C5_FIELD: J215.1, R205.2
CAP_C5_RAW: CAP1.22, R205.1
CAP_C6_FIELD: J216.1, R206.2
CAP_C6_RAW: CAP1.23, R206.1
CAP_C7_FIELD: J217.1, R207.2
CAP_C7_RAW: CAP1.24, R207.1
CAP_C8_FIELD: J218.1, R208.2
CAP_C8_RAW: CAP1.25, R208.1
CAP_CS: CAP1.15, MOD1.18
CAP_IRQ: MOD1.13, R210.1
CAP_MISO: CAP1.1, MOD1.17, U250.2
CAP_MOSI: CAP1.14, MOD1.7, U250.5
CAP_RESET: CAP1.16, MOD1.29, R209.1
CAP_SCK: CAP1.2, MOD1.8, U250.6
CH1_CS_DIS: R1108.1, U1.6
CH1_CS_RAW: R1109.1, R1110.1, U1.8
CH1_CURRENT_ADC: C1103.1, D1101.3, MOD1.20, R1110.2
CH1_DIAG: MOD1.27, R1107.1, U1.5, U1.9
CH1_INA: R1101.2, R1104.1, U1.4
CH1_INA_MCU: MOD1.2, R1101.1
CH1_INB: R1102.2, R1105.1, U1.10
CH1_INB_MCU: MOD1.12, R1102.1
CH1_OUTA: J9.1, U1.1, U1.25, U1.30
CH1_OUTB: J9.2, U1.15, U1.16, U1.21
CH1_PWM: R1103.2, R1106.1, U1.7
CH1_PWM_MCU: MOD1.22, R1103.1
CH2_CS_DIS: R1208.1, U2.6
CH2_CS_RAW: R1209.1, R1210.1, U2.8
CH2_CURRENT_ADC: C1203.1, D1201.3, MOD1.10, R1210.2
CH2_DIAG: MOD1.3, R1207.1, U2.5, U2.9
CH2_INA: R1201.2, R1204.1, U2.4
CH2_INA_MCU: MOD1.26, R1201.1
CH2_INB: R1202.2, R1205.1, U2.10
CH2_INB_MCU: MOD1.36, R1202.1
CH2_OUTA: J10.1, U2.1, U2.25, U2.30
CH2_OUTB: J10.2, U2.15, U2.16, U2.21
CH2_PWM: R1203.2, R1206.1, U2.7
CH2_PWM_MCU: MOD1.32, R1203.1
CH3_CS_DIS: R1308.1, U3.6
CH3_CS_RAW: R1309.1, R1310.1, U3.8
CH3_CURRENT_ADC: C1303.1, D1301.3, MOD2.20, R1310.2
CH3_DIAG: MOD2.27, R1307.1, U3.5, U3.9
CH3_INA: R1301.2, R1304.1, U3.4
CH3_INA_MCU: MOD2.2, R1301.1
CH3_INB: R1302.2, R1305.1, U3.10
CH3_INB_MCU: MOD2.12, R1302.1
CH3_OUTA: J11.1, U3.1, U3.25, U3.30
CH3_OUTB: J11.2, U3.15, U3.16, U3.21
CH3_PWM: R1303.2, R1306.1, U3.7
CH3_PWM_MCU: MOD2.22, R1303.1
CH4_CS_DIS: R1408.1, U4.6
CH4_CS_RAW: R1409.1, R1410.1, U4.8
CH4_CURRENT_ADC: C1403.1, D1401.3, MOD2.10, R1410.2
CH4_DIAG: MOD2.3, R1407.1, U4.5, U4.9
CH4_INA: R1401.2, R1404.1, U4.4
CH4_INA_MCU: MOD2.26, R1401.1
CH4_INB: R1402.2, R1405.1, U4.10
CH4_INB_MCU: MOD2.36, R1402.1
CH4_OUTA: J12.1, U4.1, U4.25, U4.30
CH4_OUTB: J12.2, U4.15, U4.16, U4.21
CH4_PWM: R1403.2, R1406.1, U4.7
CH4_PWM_MCU: MOD2.32, R1403.1
CH5_CS_DIS: R1508.1, U5.6
CH5_CS_RAW: R1509.1, R1510.1, U5.8
CH5_CURRENT_ADC: C1503.1, D1501.3, MOD3.20, R1510.2
CH5_DIAG: MOD3.27, R1507.1, U5.5, U5.9
CH5_INA: R1501.2, R1504.1, U5.4
CH5_INA_MCU: MOD3.2, R1501.1
CH5_INB: R1502.2, R1505.1, U5.10
CH5_INB_MCU: MOD3.12, R1502.1
CH5_OUTA: J13.1, U5.1, U5.25, U5.30
CH5_OUTB: J13.2, U5.15, U5.16, U5.21
CH5_PWM: R1503.2, R1506.1, U5.7
CH5_PWM_MCU: MOD3.22, R1503.1
CH6_CS_DIS: R1608.1, U6.6
CH6_CS_RAW: R1609.1, R1610.1, U6.8
CH6_CURRENT_ADC: C1603.1, D1601.3, MOD3.10, R1610.2
CH6_DIAG: MOD3.3, R1607.1, U6.5, U6.9
CH6_INA: R1601.2, R1604.1, U6.4
CH6_INA_MCU: MOD3.26, R1601.1
CH6_INB: R1602.2, R1605.1, U6.10
CH6_INB_MCU: MOD3.36, R1602.1
CH6_OUTA: J14.1, U6.1, U6.25, U6.30
CH6_OUTB: J14.2, U6.15, U6.16, U6.21
CH6_PWM: R1603.2, R1606.1, U6.7
CH6_PWM_MCU: MOD3.32, R1603.1
CH7_CS_DIS: R1708.1, U7.6
CH7_CS_RAW: R1709.1, R1710.1, U7.8
CH7_CURRENT_ADC: C1703.1, D1701.3, MOD4.20, R1710.2
CH7_DIAG: MOD4.27, R1707.1, U7.5, U7.9
CH7_INA: R1701.2, R1704.1, U7.4
CH7_INA_MCU: MOD4.2, R1701.1
CH7_INB: R1702.2, R1705.1, U7.10
CH7_INB_MCU: MOD4.12, R1702.1
CH7_OUTA: J15.1, U7.1, U7.25, U7.30
CH7_OUTB: J15.2, U7.15, U7.16, U7.21
CH7_PWM: R1703.2, R1706.1, U7.7
CH7_PWM_MCU: MOD4.22, R1703.1
CH8_CS_DIS: R1808.1, U8.6
CH8_CS_RAW: R1809.1, R1810.1, U8.8
CH8_CURRENT_ADC: C1803.1, D1801.3, MOD4.10, R1810.2
CH8_DIAG: MOD4.3, R1807.1, U8.5, U8.9
CH8_INA: R1801.2, R1804.1, U8.4
CH8_INA_MCU: MOD4.26, R1801.1
CH8_INB: R1802.2, R1805.1, U8.10
CH8_INB_MCU: MOD4.36, R1802.1
CH8_OUTA: J16.1, U8.1, U8.25, U8.30
CH8_OUTB: J16.2, U8.15, U8.16, U8.21
CH8_PWM: R1803.2, R1806.1, U8.7
CH8_PWM_MCU: MOD4.32, R1803.1
EEPROM_CS: MOD1.35, R260.1, U250.1
EEPROM_HOLD: R262.1, U250.7
EEPROM_WP: R261.1, U250.3
ESP_CAN_RX_GPIO38: CAN2.4, ESP1.35
ESP_CAN_TX_GPIO39: CAN2.3, ESP1.36
FUSED_12V_CH1: C1101.1, C1102.1, J1.1, U1.3, U1.12, U1.13, U1.23
FUSED_12V_CH2: C1201.1, C1202.1, J2.1, U2.3, U2.12, U2.13, U2.23
FUSED_12V_CH3: C1301.1, C1302.1, J3.1, U3.3, U3.12, U3.13, U3.23
FUSED_12V_CH4: C1401.1, C1402.1, J4.1, U4.3, U4.12, U4.13, U4.23
FUSED_12V_CH5: C1501.1, C1502.1, J5.1, U5.3, U5.12, U5.13, U5.23
FUSED_12V_CH6: C1601.1, C1602.1, J6.1, U6.3, U6.12, U6.13, U6.23
FUSED_12V_CH7: C1701.1, C1702.1, J7.1, U7.3, U7.12, U7.13, U7.23
FUSED_12V_CH8: C1801.1, C1802.1, J8.1, U8.3, U8.12, U8.13, U8.23
GND: C230.2, C231.2, C232.2, C233.2, C234.2, C235.2, C236.2, C237.2, C238.2, C239.2, C250.2, C1101.2, C1102.2, C1103.2, C1201.2, C1202.2, C1203.2, C1301.2, C1302.2, C1303.2, C1401.2, C1402.2, C1403.2, C1501.2, C1502.2, C1503.2, C1601.2, C1602.2, C1603.2, C1701.2, C1702.2, C1703.2, C1801.2, C1802.2, C1803.2, CAN1.2, CAN2.2, CAP1.4, CAP1.26, D231.2, D240.2, D241.2, D1101.1, D1201.1, D1301.1, D1401.1, D1501.1, D1601.1, D1701.1, D1801.1, DC1.2, DC1.4, ESP1.22, ESP1.23, ESP1.24, ESP1.44, J1.2, J2.2, J3.2, J4.2, J5.2, J6.2, J7.2, J8.2, J201.3, J202.3, J203.3, J204.3, J205.3, J206.3, J211.2, J212.2, J213.2, J214.2, J215.2, J216.2, J217.2, J218.2, J220.5, J230.2, J240.3, J240.4, MOD1.1, MOD1.31, MOD2.1, MOD2.31, MOD3.1, MOD3.31, MOD4.1, MOD4.31, R209.2, R1104.2, R1105.2, R1106.2, R1108.2, R1109.2, R1204.2, R1205.2, R1206.2, R1208.2, R1209.2, R1304.2, R1305.2, R1306.2, R1308.2, R1309.2, R1404.2, R1405.2, R1406.2, R1408.2, R1409.2, R1504.2, R1505.2, R1506.2, R1508.2, R1509.2, R1604.2, R1605.2, R1606.2, R1608.2, R1609.2, R1704.2, R1705.2, R1706.2, R1708.2, R1709.2, R1804.2, R1805.2, R1806.2, R1808.2, R1809.2, R3021.2, R3032.2, R3041.2, R3042.2, RF1.4, U1.18, U1.19, U1.20, U1.26, U1.27, U1.28, U2.18, U2.19, U2.20, U2.26, U2.27, U2.28, U3.18, U3.19, U3.20, U3.26, U3.27, U3.28, U4.18, U4.19, U4.20, U4.26, U4.27, U4.28, U5.18, U5.19, U5.20, U5.26, U5.27, U5.28, U6.18, U6.19, U6.20, U6.26, U6.27, U6.28, U7.18, U7.19, U7.20, U7.26, U7.27, U7.28, U8.18, U8.19, U8.20, U8.26, U8.27, U8.28, U230.1, U250.4
LOGIC_3V3: C238.1, C239.1, C250.1, CAN1.1, CAN2.1, R260.2, R261.2, R262.2, RF1.2, U230.2, U250.8
LOGIC_5V: C233.1, C234.1, C235.1, C236.1, C237.1, CAP1.3, DC1.3, ESP1.21, MOD1.21, MOD2.21, MOD3.21, MOD4.21, U230.3
LOGIC_12V_FUSED: D230.1, F230.2
LOGIC_12V_IN: F230.1, J230.1
LOGIC_12V_PROTECTED: C230.1, C231.1, C232.1, D230.2, D231.1, DC1.1
REED_A_CLOSED: J202.2, MOD1.5
REED_A_IN_PLACE: J203.2, MOD1.38
REED_A_OPEN: J201.2, MOD1.6
REED_B_CLOSED: J205.2, MOD2.5
REED_B_IN_PLACE: J206.2, MOD2.38
REED_B_OPEN: J204.2, MOD2.6
RF_CSN: ESP1.16, RF1.3
RF_GDO0: ESP1.4, RF1.1
RF_GDO2: ESP1.5, RF1.8
RF_MISO: ESP1.19, RF1.7
RF_MOSI: ESP1.17, RF1.6
RF_SCK: ESP1.18, RF1.5
S1_3V3: D1101.2, D1201.2, J201.1, J202.1, J203.1, J220.1, MOD1.11, R210.2, R1107.2, R1207.2, R3011.2, R3012.2
S1_CAN_RX: CAN1.4, MOD1.33
S1_CAN_TX: CAN1.3, MOD1.24
S1_NRST: J220.4, MOD1.16
S1_SLOT_ID0: MOD1.15, R3011.1
S1_SWCLK: J220.3, MOD1.25
S1_SWDIO: J220.2, MOD1.34
S1_UART1_RX: MOD1.28, R251.2
S1_UART1_TX: MOD1.37, R250.1
S1_UART2_RX: MOD1.9, R253.2
S1_UART2_TX: MOD1.19, R252.1
S1_UART3_RX: MOD1.14, R255.2
S1_UART3_TX: MOD1.4, R254.1
S2_3V3: D1301.2, D1401.2, J204.1, J205.1, J206.1, MOD2.11, R1307.2, R1407.2, R3022.2
S2_SLOT_ID0: MOD2.15, R3021.1
S2_SLOT_ID1: MOD2.7, R3022.1
S2_UART_RX: MOD2.28, R250.2
S2_UART_TX: MOD2.37, R251.1
S3_3V3: D1501.2, D1601.2, MOD3.11, R1507.2, R1607.2, R3031.2
S3_SLOT_ID0: MOD3.15, R3031.1
S3_SLOT_ID1: MOD3.7, R3032.1
S3_UART_RX: MOD3.28, R252.2
S3_UART_TX: MOD3.37, R253.1
S4_3V3: D1701.2, D1801.2, MOD4.11, R1707.2, R1807.2
S4_SLOT_ID0: MOD4.15, R3041.1
S4_SLOT_ID1: MOD4.7, R3042.1
S4_UART_RX: MOD4.28, R254.2
S4_UART_TX: MOD4.37, R255.1

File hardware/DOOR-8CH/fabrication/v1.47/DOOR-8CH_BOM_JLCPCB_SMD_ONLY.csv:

"Comment","Designator","Footprint","LCSC Part #"
"1uF 50V X7R 1206; CCTC TCC1206X7R105M500FT","C231","C_1206_3216Metric","C5448921"
"100nF 50V X7R; YAGEO CC0603KRX7R9BB104","C232,C235,C237,C239,C250,C270,C271,C1102,C1103,C1202,C1203,C1302,C1303,C1402,C1403,C1502,C1503,C1602,C1603,C1702,C1703,C1802,C1803","C_0603_1608Metric","C14663"
"10uF 25V X7R 1206; YAGEO CC1206KKX7R8BB106","C234,C236,C238","C_1206_3216Metric","C70462"
"BAT54S dual series Schottky SOT-23; Nexperia BAT54S,215","D1101,D1201,D1301,D1401,D1501,D1601,D1701,D1801","SOT-23","C47546"
"SS54 5A 40V SMB; LGE SS54","D230","D_SMB","C432139"
"SMBJ16A 600W unidirectional SMB; LGE SMBJ16A","D231","D_SMB","C713715"
"24V bidirectional low-capacitance CAN ESD SOD-323; Yint ESD24VD3B","D240,D241","D_SOD-323","C484324"
"CAN common-mode choke 100uH 1812; TDK ACT45B-101-2P-TL003","L240","L_CommonModeChoke_Coilcraft_1812CAN","C88056"
"4.7K 1% 0603; UNI-ROYAL 0603WAF4701T5E","R1107,R1207,R1307,R1407,R1507,R1607,R1707,R1807","R_0603_1608Metric","C23162"
"1K 1% 0603; UNI-ROYAL 0603WAF1001T5E","R201,R202,R203,R204,R205,R206,R207,R208,R1109,R1209,R1309,R1409,R1509,R1609,R1709,R1809","R_0603_1608Metric","C21190"
"10K 1% 0603; UNI-ROYAL 0603WAF1002T5E","R209,R210,R260,R261,R262,R271,R272,R1104,R1105,R1106,R1108,R1110,R1204,R1205,R1206,R1208,R1210,R1304,R1305,R1306,R1308,R1310,R1404,R1405,R1406,R1408,R1410,R1504,R1505,R1506,R1508,R1510,R1604,R1605,R1606,R1608,R1610,R1704,R1705,R1706,R1708,R1710,R1804,R1805,R1806,R1808,R1810","R_0603_1608Metric","C25804"
"100R 1% 0603; UNI-ROYAL 0603WAF1000T5E","R250,R251,R252,R253,R254,R255,R1101,R1102,R1103,R1201,R1202,R1203,R1301,R1302,R1303,R1401,R1402,R1403,R1501,R1502,R1503,R1601,R1602,R1603,R1701,R1702,R1703,R1801,R1802,R1803","R_0603_1608Metric","C22775"
"226K 1% 0603; FH RS-03K2263FT","R270","R_0603_1608Metric","C321793"
"47K 1% 0603; UNI-ROYAL 0603WAF4702T5E","R3011,R3012,R3022,R3031","R_0603_1608Metric","C25819"
"0R 0603; UNI-ROYAL 0603WAF0000T5E","R3021,R3032,R3041,R3042","R_0603_1608Metric","C21189"
"AMS1117-3.3 SOT-223","U230","SOT-223-3_TabPin2","C6186"
"25LC256-I/SN SPI EEPROM SOIC-8","U250","SOIC-8_3.9x4.9mm_P1.27mm","C84670"
"TLV6700DDCR power monitor TSOT-23-6","U270","SOT-23-6","C2868382"

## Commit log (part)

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2026-06-15 Add RF button target mapping
2026-06-15 Add main page RP2040 target selector
2026-06-16 Show RS485 node safety diagnostics
2026-06-17 Add per-node CAP1188 settings
2026-06-19 Support two local RP2040 UART nodes
2026-06-19 Split local RP2040 current settings
2026-06-19 Use per-actuator relay direction outputs
2026-06-21 Compact ESP32 web config layout
2026-06-21 Show RF action settings conditionally
2026-06-21 Apply dark web interface theme
2026-06-21 Use active-low RP2040 relay outputs
2026-06-21 Reduce RF remote command latency
2026-06-21 Repeat web window commands reliably
2026-06-21 Add RP2040 command diagnostics
2026-06-21 Reduce web command latency
2026-06-21 Queue web window command repeats
2026-06-21 Send web commands on pointer press
2026-06-21 Prevent web UI request stalls
2026-06-21 Add Android APK wrapper project
2026-06-21 Improve Android connection screen
2026-06-21 Remove mobile connection settings
2026-06-21 Stabilize mobile control layout
